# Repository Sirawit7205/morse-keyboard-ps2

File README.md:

# morse-keyboard-ps2
Morse Code Keyboard with logic ICs (with PS/2 Keyboard Support)

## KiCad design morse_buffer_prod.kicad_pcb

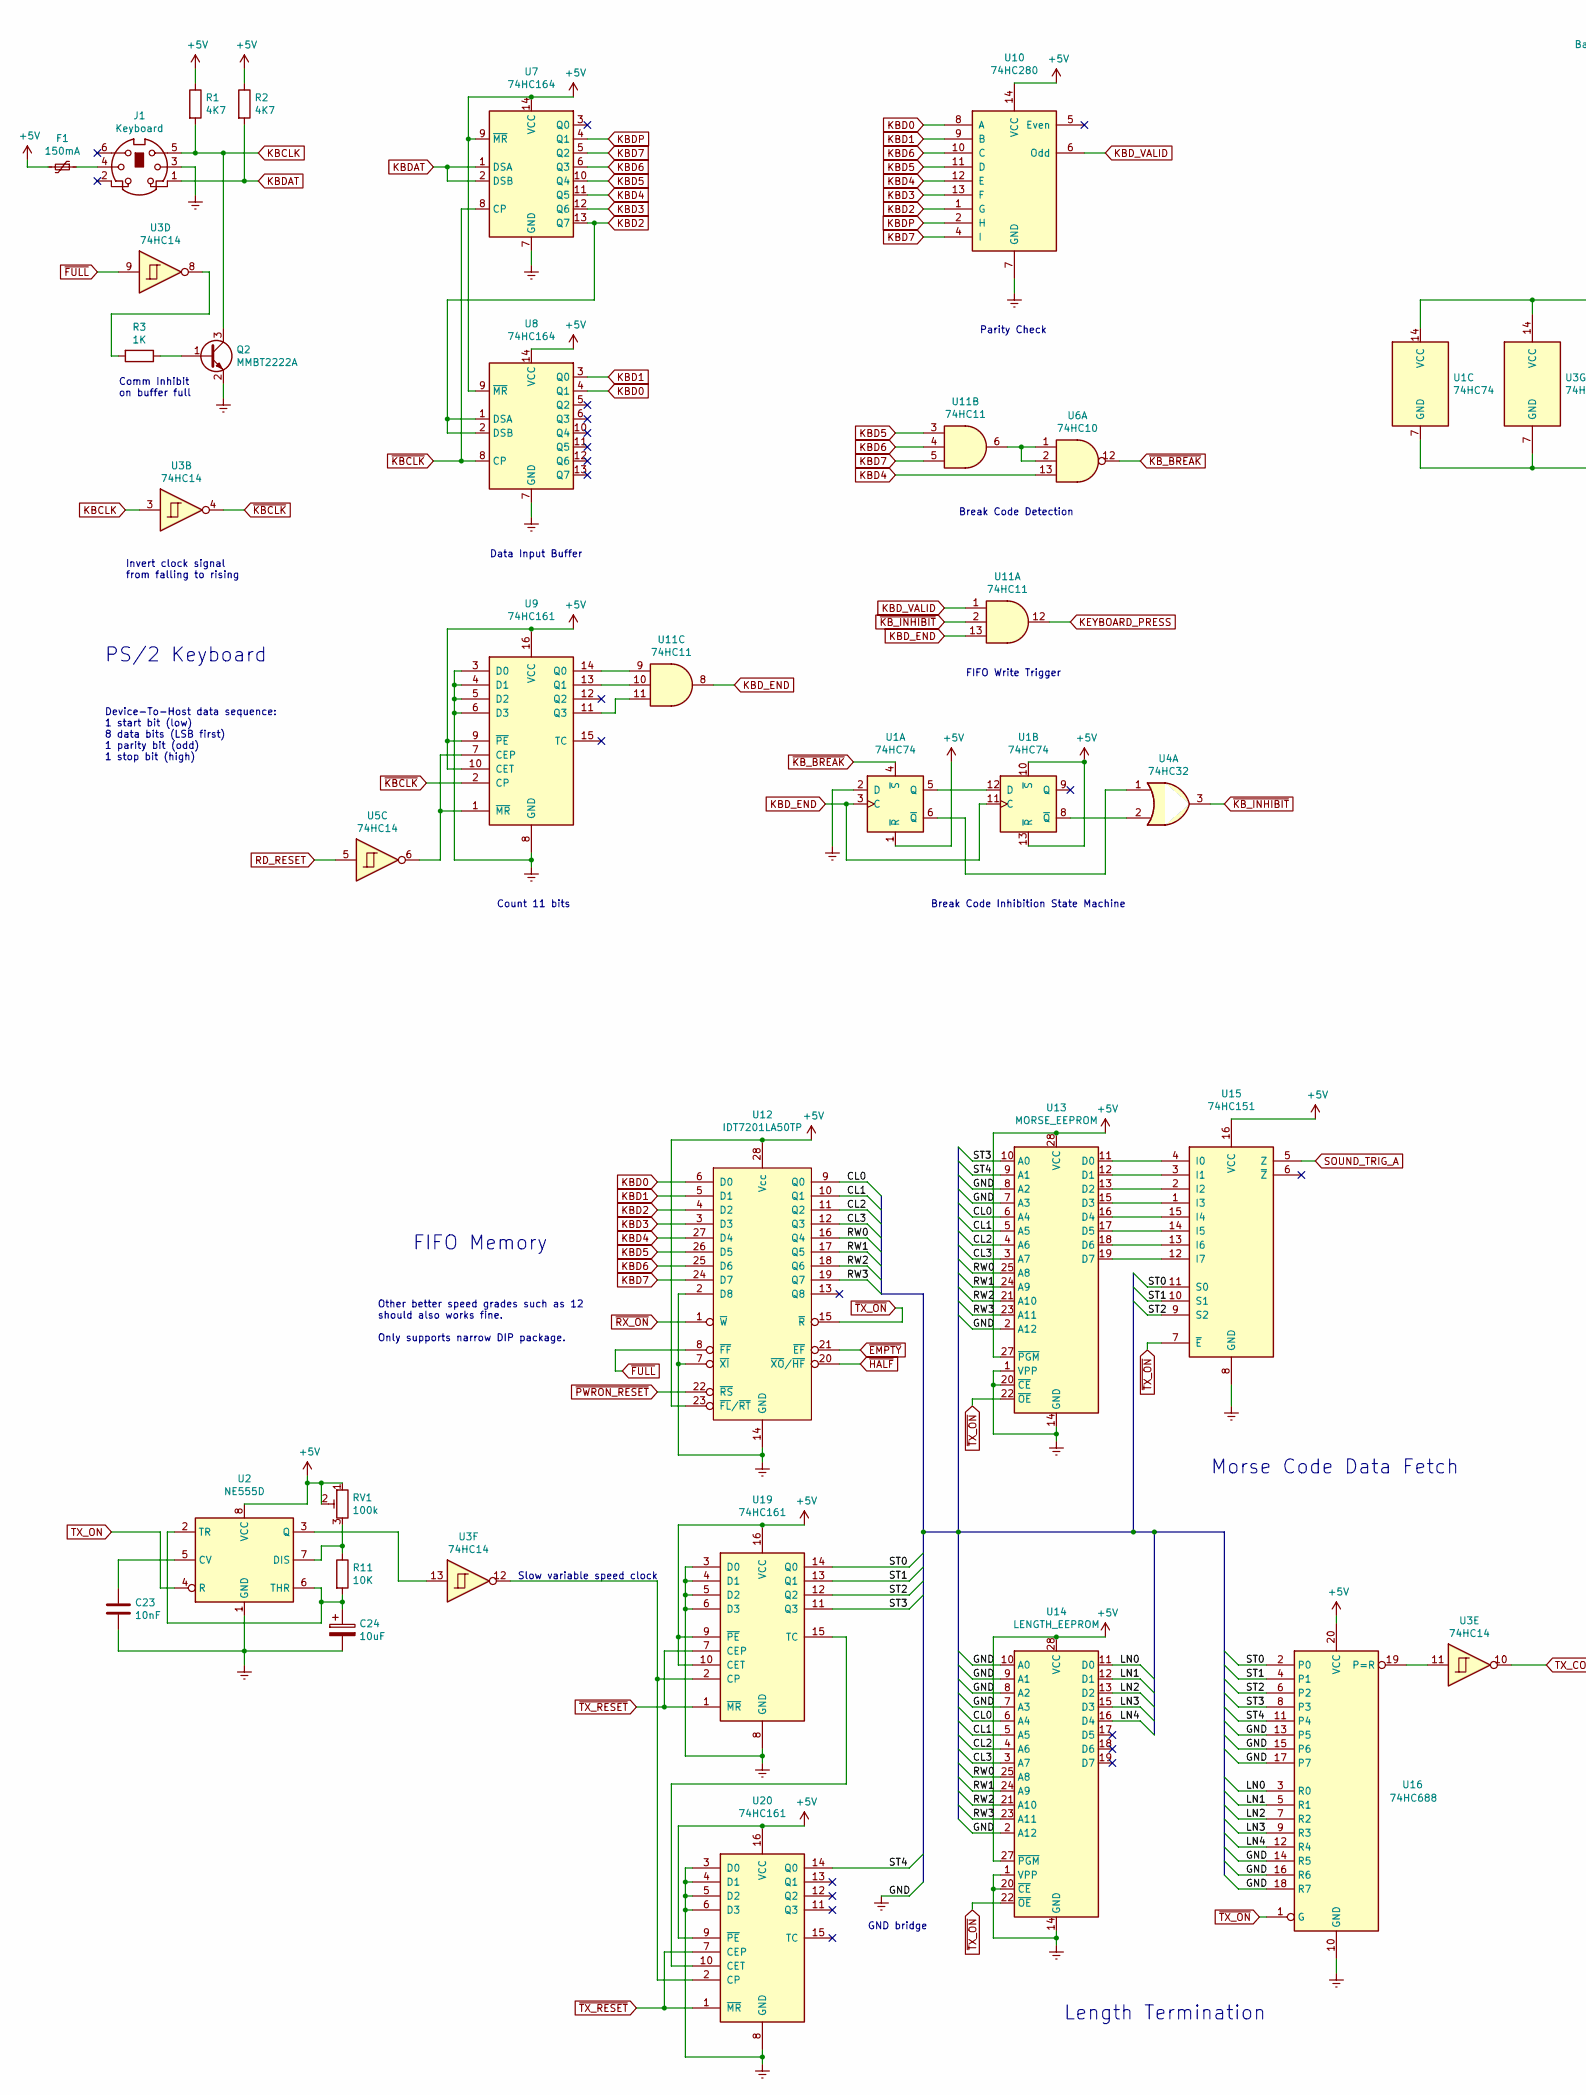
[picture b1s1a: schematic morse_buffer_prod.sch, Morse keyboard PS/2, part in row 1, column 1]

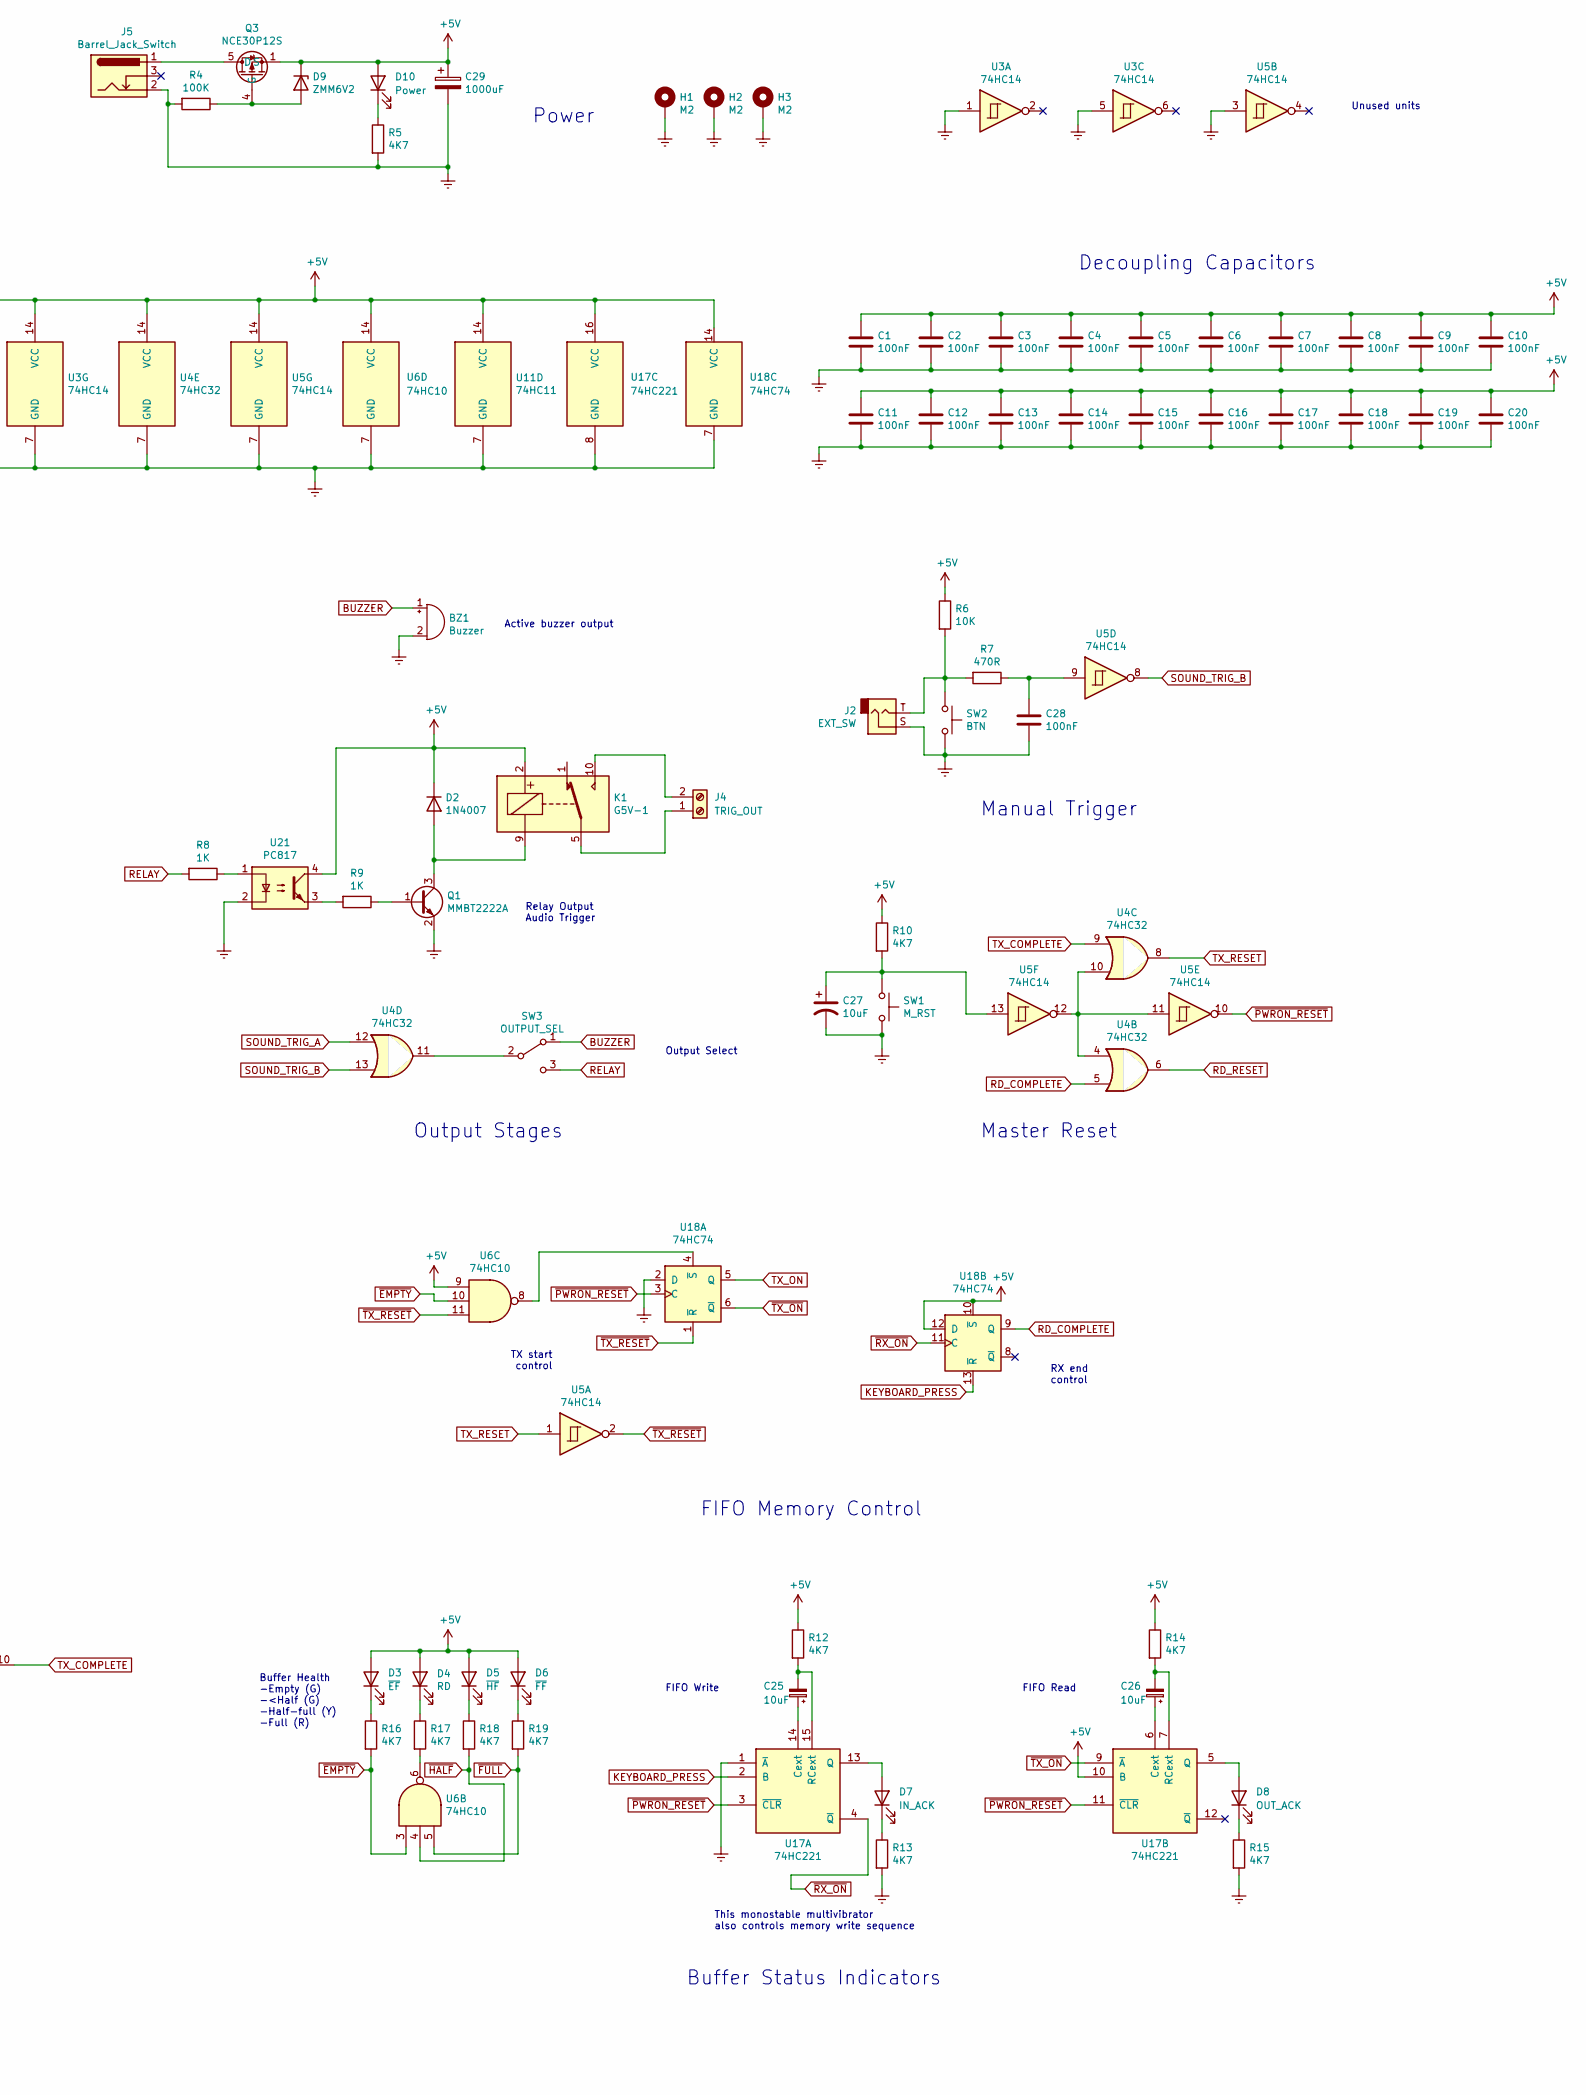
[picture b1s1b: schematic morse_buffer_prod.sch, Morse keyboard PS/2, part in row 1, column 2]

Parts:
BZ1: Buzzer; Buzzer_12x9.5RM7.6
C1, C2, C3, C4, C5, C6, C7, C8, C9, C10, C11, C12, C13, C14, C15, C16, C17, C18, C19, C20, C28: 100nF; C_0603_1608Metric
C23: 10nF; C_0603_1608Metric
C24, C25, C26, C27: 10uF; CP_Radial_D5.0mm_P2.00mm
C29: 1000uF; CP_Radial_D10.0mm_P5.00mm
D2: 1N4007; D_SOD-123F
D3: ~EF; LED_0603_1608Metric
D4: RD; LED_0603_1608Metric
D5: ~HF; LED_0603_1608Metric
D6: ~FF; LED_0603_1608Metric
D7: IN_ACK; LED_0603_1608Metric
D8: OUT_ACK; LED_0603_1608Metric
D9: ZMM6V2; D_MiniMELF
D10: Power; LED_0603_1608Metric
F1: 150mA; Fuse_1210_3225Metric
H1, H2, H3: M2; MountingHole_2.2mm_M2_Pad
J1: Keyboard; Connector_Mini-DIN_Female_6Pin_2rows
J2: EXT_SW; PJ-313
J4: TRIG_OUT; TerminalBlock_bornier-2_P5.08mm
J5: Barrel_Jack_Switch; BarrelJack_Horizontal
K1: G5V-1; Relay_SPDT_Omron_G5V-1
Q1, Q2: MMBT2222A; SOT-23
Q3: NCE30P12S; SOIC-8_3.9x4.9mm_P1.27mm
R1, R2, R5, R10, R12, R13, R14, R15, R16, R17, R18, R19: 4K7; R_0603_1608Metric
R3, R8, R9: 1K; R_0603_1608Metric
R4: 100K; R_0603_1608Metric
R6, R11: 10K; R_0603_1608Metric
R7: 470R; R_0603_1608Metric
RV1: 100k; Potentiometer_Bourns_3296W_Vertical
SW1: M_RST; SW_PUSH_6mm
SW2: BTN; SW_PUSH_6mm
SW3: OUTPUT_SEL; SW_Slide_1P2T_CK_OS102011MS2Q
U1, U18: 74HC74; SOIC-14_3.9x8.7mm_P1.27mm
U2: NE555D; SOIC-8_3.9x4.9mm_P1.27mm
U3, U5: 74HC14; SOIC-14_3.9x8.7mm_P1.27mm
U4: 74HC32; SOIC-14_3.9x8.7mm_P1.27mm
U6: 74HC10; SOIC-14_3.9x8.7mm_P1.27mm
U7, U8: 74HC164; SOIC-14_3.9x8.7mm_P1.27mm
U9, U19, U20: 74HC161; SOIC-16_3.9x9.9mm_P1.27mm
U10: 74HC280; SOIC-14_3.9x8.7mm_P1.27mm
U11: 74HC11; SOIC-14_3.9x8.7mm_P1.27mm
U12: IDT7201LA50TP; DIP-28_W7.62mm
U13: MORSE_EEPROM; SOIC-28W_7.5x17.9mm_P1.27mm
U14: LENGTH_EEPROM; SOIC-28W_7.5x17.9mm_P1.27mm
U15: 74HC151; SOIC-16_3.9x9.9mm_P1.27mm
U16: 74HC688; SOIC-20W_7.5x12.8mm_P1.27mm
U17: 74HC221; SOIC-16_3.9x9.9mm_P1.27mm
U21: PC817; DIP-4_W7.62mm

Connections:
+5V: C1.1, C2.1, C3.1, C4.1, C5.1, C6.1, C7.1, C8.1, C9.1, C10.1, C11.1, C12.1, C13.1, C14.1, C15.1, C16.1, C17.1, C18.1, C19.1, C20.1, C29.1, D2.1 (K), D3.2 (A), D4.2 (A), D5.2 (A), D6.2 (A), D9.1 (K), D10.2 (A), F1.2, K1.2, Q3.1 (S), Q3.2 (S), Q3.3 (S), R1.1, R2.1, R6.1, R10.1, R12.1, R14.1, RV1.1, RV1.2, U1.1 (~R), U1.10 (~S), U1.13 (~R), U1.14 (VCC), U2.8 (VCC), U3.14 (VCC), U4.14 (VCC), U5.14 (VCC), U6.9, U6.14 (VCC), U7.9 (~MR), U7.14 (VCC), U8.9 (~MR), U8.14 (VCC), U9.9 (~PE), U9.10 (CET), U9.16 (VCC), U10.14 (VCC), U11.14 (VCC), U12.23 (~FL~/~RT), U12.28 (Vcc), U13.27 (~PGM), U13.28 (VCC), U14.27 (~PGM), U14.28 (VCC), U15.16 (VCC), U16.20 (VCC), U17.10 (B), U17.16 (VCC), U18.10 (~S), U18.12 (D), U18.14 (VCC), U19.9 (~PE), U19.10 (CET), U19.16 (VCC), U20.9 (~PE), U20.16 (VCC), U21.4
/CL0: U12.9 (Q0), U13.6 (A4), U14.6 (A4)
/CL1: U12.10 (Q1), U13.5 (A5), U14.5 (A5)
/CL2: U12.11 (Q2), U13.4 (A6), U14.4 (A6)
/CL3: U12.12 (Q3), U13.3 (A7), U14.3 (A7)
/LN0: U14.11 (D0), U16.3 (R0)
/LN1: U14.12 (D1), U16.5 (R1)
/LN2: U14.13 (D2), U16.7 (R2)
/LN3: U14.15 (D3), U16.9 (R3)
/LN4: U14.16 (D4), U16.12 (R4)
/RW0: U12.16 (Q4), U13.25 (A8), U14.25 (A8)
/RW1: U12.17 (Q5), U13.24 (A9), U14.24 (A9)
/RW2: U12.18 (Q6), U13.21 (A10), U14.21 (A10)
/RW3: U12.19 (Q7), U13.23 (A11), U14.23 (A11)
/ST0: U15.11 (S0), U16.2 (P0), U19.14 (Q0)
/ST1: U15.10 (S1), U16.4 (P1), U19.13 (Q1)
/ST2: U15.9 (S2), U16.6 (P2), U19.12 (Q2)
/ST3: U13.10 (A0), U16.8 (P3), U19.11 (Q3)
/ST4: U13.9 (A1), U16.11 (P4), U20.14 (Q0)
BUZZER: BZ1.1 (-), SW3.1 (A)
GNDREF: BZ1.2 (+), C1.2, C2.2, C3.2, C4.2, C5.2, C6.2, C7.2, C8.2, C9.2, C10.2, C11.2, C12.2, C13.2, C14.2, C15.2, C16.2, C17.2, C18.2, C19.2, C20.2, C23.2, C24.2, C27.2, C28.2, C29.2, H1.1, H2.1, H3.1, J1.3, J2.S, J5.2, Q1.2 (E), Q2.2 (E), R4.2, R5.2, R13.2, R15.2, SW1.2, SW2.2, U1.2 (D), U1.7 (GND), U2.1 (GND), U3.1, U3.5, U3.7 (GND), U4.7 (GND), U5.3, U5.7 (GND), U6.7 (GND), U7.7 (GND), U8.7 (GND), U9.3 (D0), U9.4 (D1), U9.5 (D2), U9.6 (D3), U9.8 (GND), U10.7 (GND), U11.7 (GND), U12.2 (D8), U12.7 (~XI), U12.14 (GND), U13.1 (VPP), U13.2 (A12), U13.7 (A3), U13.8 (A2), U13.14 (GND), U13.20 (~CE), U14.1 (VPP), U14.2 (A12), U14.7 (A3), U14.8 (A2), U14.9 (A1), U14.10 (A0), U14.14 (GND), U14.20 (~CE), U15.8 (GND), U16.10 (GND), U16.13 (P5), U16.14 (R5), U16.15 (P6), U16.16 (R6), U16.17 (P7), U16.18 (R7), U17.1 (~A), U17.8 (GND), U18.2 (D), U18.7 (GND), U19.3 (D0), U19.4 (D1), U19.5 (D2), U19.6 (D3), U19.8 (GND), U20.3 (D0), U20.4 (D1), U20.5 (D2), U20.6 (D3), U20.8 (GND), U21.2
KBCLK: J1.5, Q2.3 (C), R1.2, U3.3
KBD0: U8.4 (Q1), U10.8 (A), U12.6 (D0)
KBD1: U8.3 (Q0), U10.9 (B), U12.5 (D1)
KBD2: U7.13 (Q7), U8.1 (DSA), U8.2 (DSB), U10.1 (G), U12.4 (D2)
KBD3: U7.12 (Q6), U10.13 (F), U12.3 (D3)
KBD4: U6.13, U7.11 (Q5), U10.12 (E), U12.27 (D4)
KBD5: U7.10 (Q4), U10.11 (D), U11.3, U12.26 (D5)
KBD6: U7.6 (Q3), U10.10 (C), U11.4, U12.25 (D6)
KBD7: U7.5 (Q2), U10.4 (I), U11.5, U12.24 (D7)
KBDAT: J1.1, R2.2, U7.1 (DSA), U7.2 (DSB)
KBDP: U7.4 (Q1), U10.2 (H)
KBD_END: U1.3 (C), U1.11 (C), U11.8, U11.13
KBD_VALID: U10.6 (Odd), U11.1
KEYBOARD_PRESS: U11.12, U17.2 (B), U18.13 (~R)
unnamed: C23.1, U2.5 (CV)
unnamed: C24.1, R11.2, U2.2 (TR), U2.6 (THR)
unnamed: C25.1, U17.14 (Cext)
unnamed: C25.2, R12.2, U17.15 (RCext)
unnamed: C26.1, U17.6 (Cext)
unnamed: C26.2, R14.2, U17.7 (RCext)
unnamed: C27.1, R10.2, SW1.1, U5.13
unnamed: C28.1, R7.1, U5.9
unnamed: D2.2 (A), K1.9, Q1.3 (C)
unnamed: D3.1 (K), R16.1
unnamed: D4.1 (K), R17.1
unnamed: D5.1 (K), R18.1
unnamed: D6.1 (K), R19.1
unnamed: D7.1 (K), R13.1
unnamed: D7.2 (A), U17.13 (Q)
unnamed: D8.1 (K), R15.1
unnamed: D8.2 (A), U17.5 (Q)
unnamed: D9.2 (A), Q3.4 (G), R4.1
unnamed: D10.1 (K), R5.1
unnamed: F1.1, J1.4
unnamed: J2.T, R6.2, R7.2, SW2.1
unnamed: J4.1, K1.5, K1.6
unnamed: J4.2, K1.10
unnamed: J5.1, Q3.5 (D), Q3.6 (D), Q3.7 (D), Q3.8 (D)
unnamed: Q1.1 (B), R9.1
unnamed: Q2.1 (B), R3.1
unnamed: R3.2, U3.8
unnamed: R8.1, U21.1
unnamed: R9.2, U21.3
unnamed: R11.1, RV1.3, U2.7 (DIS)
unnamed: R17.2, U6.6
unnamed: SW3.2 (B), U4.11
unnamed: U1.6 (~Q), U4.1
unnamed: U1.8 (~Q), U4.2
unnamed: U1.5 (Q), U1.12 (D)
unnamed: U2.3 (Q), U3.13
unnamed: U4.4, U4.10, U5.11, U5.12
unnamed: U5.6, U9.1 (~MR), U9.7 (CEP)
unnamed: U6.1, U6.2, U11.6
unnamed: U9.14 (Q0), U11.9
unnamed: U9.13 (Q1), U11.10
unnamed: U9.11 (Q3), U11.11
unnamed: U13.11 (D0), U15.4 (I0)
unnamed: U13.12 (D1), U15.3 (I1)
unnamed: U13.13 (D2), U15.2 (I2)
unnamed: U13.15 (D3), U15.1 (I3)
unnamed: U13.16 (D4), U15.15 (I4)
unnamed: U13.17 (D5), U15.14 (I5)
unnamed: U13.18 (D6), U15.13 (I6)
unnamed: U13.19 (D7), U15.12 (I7)
unnamed: U3.11, U16.19 (P=R)
unnamed: U6.8, U18.4 (~S)
unnamed: U3.12, U19.2 (CP), U20.2 (CP)
unnamed: U19.15 (TC), U20.10 (CET)
RD_COMPLETE: U4.5, U18.9 (Q)
RD_RESET: U4.6, U5.5
RELAY: R8.2, SW3.3 (C)
SOUND_TRIG_A: U4.12, U15.5 (Z)
SOUND_TRIG_B: U4.13, U5.8
TX_COMPLETE: U3.10, U4.9
TX_ON: U2.4 (R), U18.5 (Q)
TX_RESET: U4.8, U5.1
~EMPTY: R16.2, U6.3, U6.10, U12.21 (~EF)
~FULL: R19.2, U3.9, U6.5, U12.8 (~FF)
~HALF: R18.2, U6.4, U12.20 (~XO~/~HF)
~KBCLK: U3.4, U7.8 (CP), U8.8 (CP), U9.2 (CP)
~KB_BREAK: U1.4 (~S), U6.12
~KB_INHIBIT: U4.3, U11.2
~PWRON_RESET: U5.10, U12.22 (~RS), U17.3 (~CLR), U17.11 (~CLR), U18.3 (C)
~RX_ON: U12.1 (~W), U17.4 (~Q), U18.11 (C)
~TX_ON: U12.15 (~R), U13.22 (~OE), U14.22 (~OE), U15.7 (~E), U16.1 (G), U17.9 (~A), U18.6 (~Q)
~TX_RESET: U5.2, U6.11, U18.1 (~R), U19.1 (~MR), U19.7 (CEP), U20.1 (~MR), U20.7 (CEP)

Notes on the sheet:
Manual Trigger
Relay Output Audio Trigger
Output Select
Active buzzer output
Morse Code Data Fetch
Length Termination
TX start control
FIFO Memory Control
FIFO Read
FIFO Write
Buffer Status Indicators
Buffer Health -Empty (G) -<Half (G) -Half-full (Y) -Full (R)
This monostable multivibrator also controls memory write sequence
RX end control
FIFO Memory
Other better speed grades such as 12 should also works fine. Only supports narrow DIP package.
Master Reset
Slow variable speed clock
Output Stages
Power
Decoupling Capacitors
GND bridge
Count 11 bits
Parity Check
Break Code Inhibition State Machine
Break Code Detection
FIFO Write Trigger
Data Input Buffer
Unused units
Device-To-Host data sequence: 1 start bit (low) 8 data bits (LSB first) 1 parity bit (odd) 1 stop bit (high)
Invert clock signal from falling to rising
PS/2 Keyboard
Comm Inhibit on buffer full

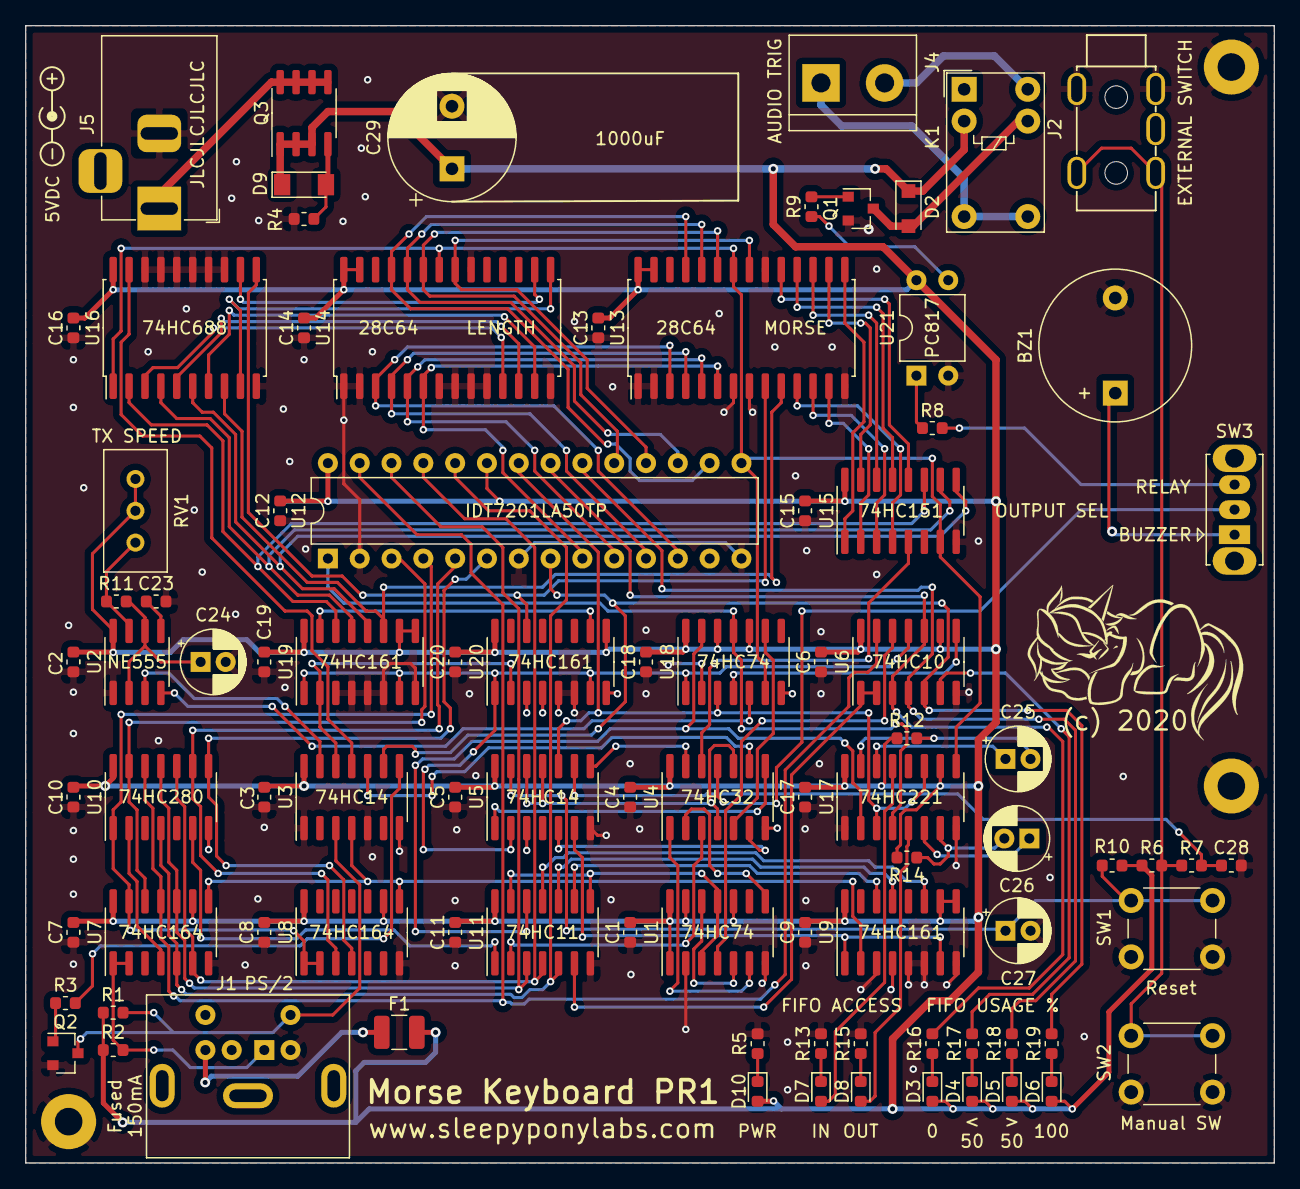
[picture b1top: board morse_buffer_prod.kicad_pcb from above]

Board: 2 copper layers, 99.7 x 90.8 mm, 93 parts (0 on the bottom side), 107 nets.

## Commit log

2021-01-03 Initial Commit, Import files from Matrix version
2021-01-03 Add gitignore
2021-01-03 Add PS/2 controller
2021-01-04 PCB routing
2021-01-04 Add fuse for ps/2 device

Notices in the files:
morse_buffer_prod.kicad_pcb:
(c) 2020
